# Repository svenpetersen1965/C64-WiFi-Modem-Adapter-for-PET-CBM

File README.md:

# C64-WiFi-Modem-Adapter for the Commodore PET/CBM computers
This is an adapter for connecting a <a href="https://github.com/svenpetersen1965/C64-WiFi-Modem-User-Port">C64 WiFi-Modem</a> to the PET/CBM User Port.

The power obtained from the Cassette Port via the <a href="https://github.com/svenpetersen1965/C64-Diagnostic-Rev.-586220-Harness/tree/master/Diag586220_Harness/Diag586220_Cassette_Port">Cassette Port Dongle</a> from the diagnostic harness for the C64.

The terminal program that was used for testing is <a href="https://github.com/ChartreuseK/PETTERM/releases">PETTERM0.5.0</a>

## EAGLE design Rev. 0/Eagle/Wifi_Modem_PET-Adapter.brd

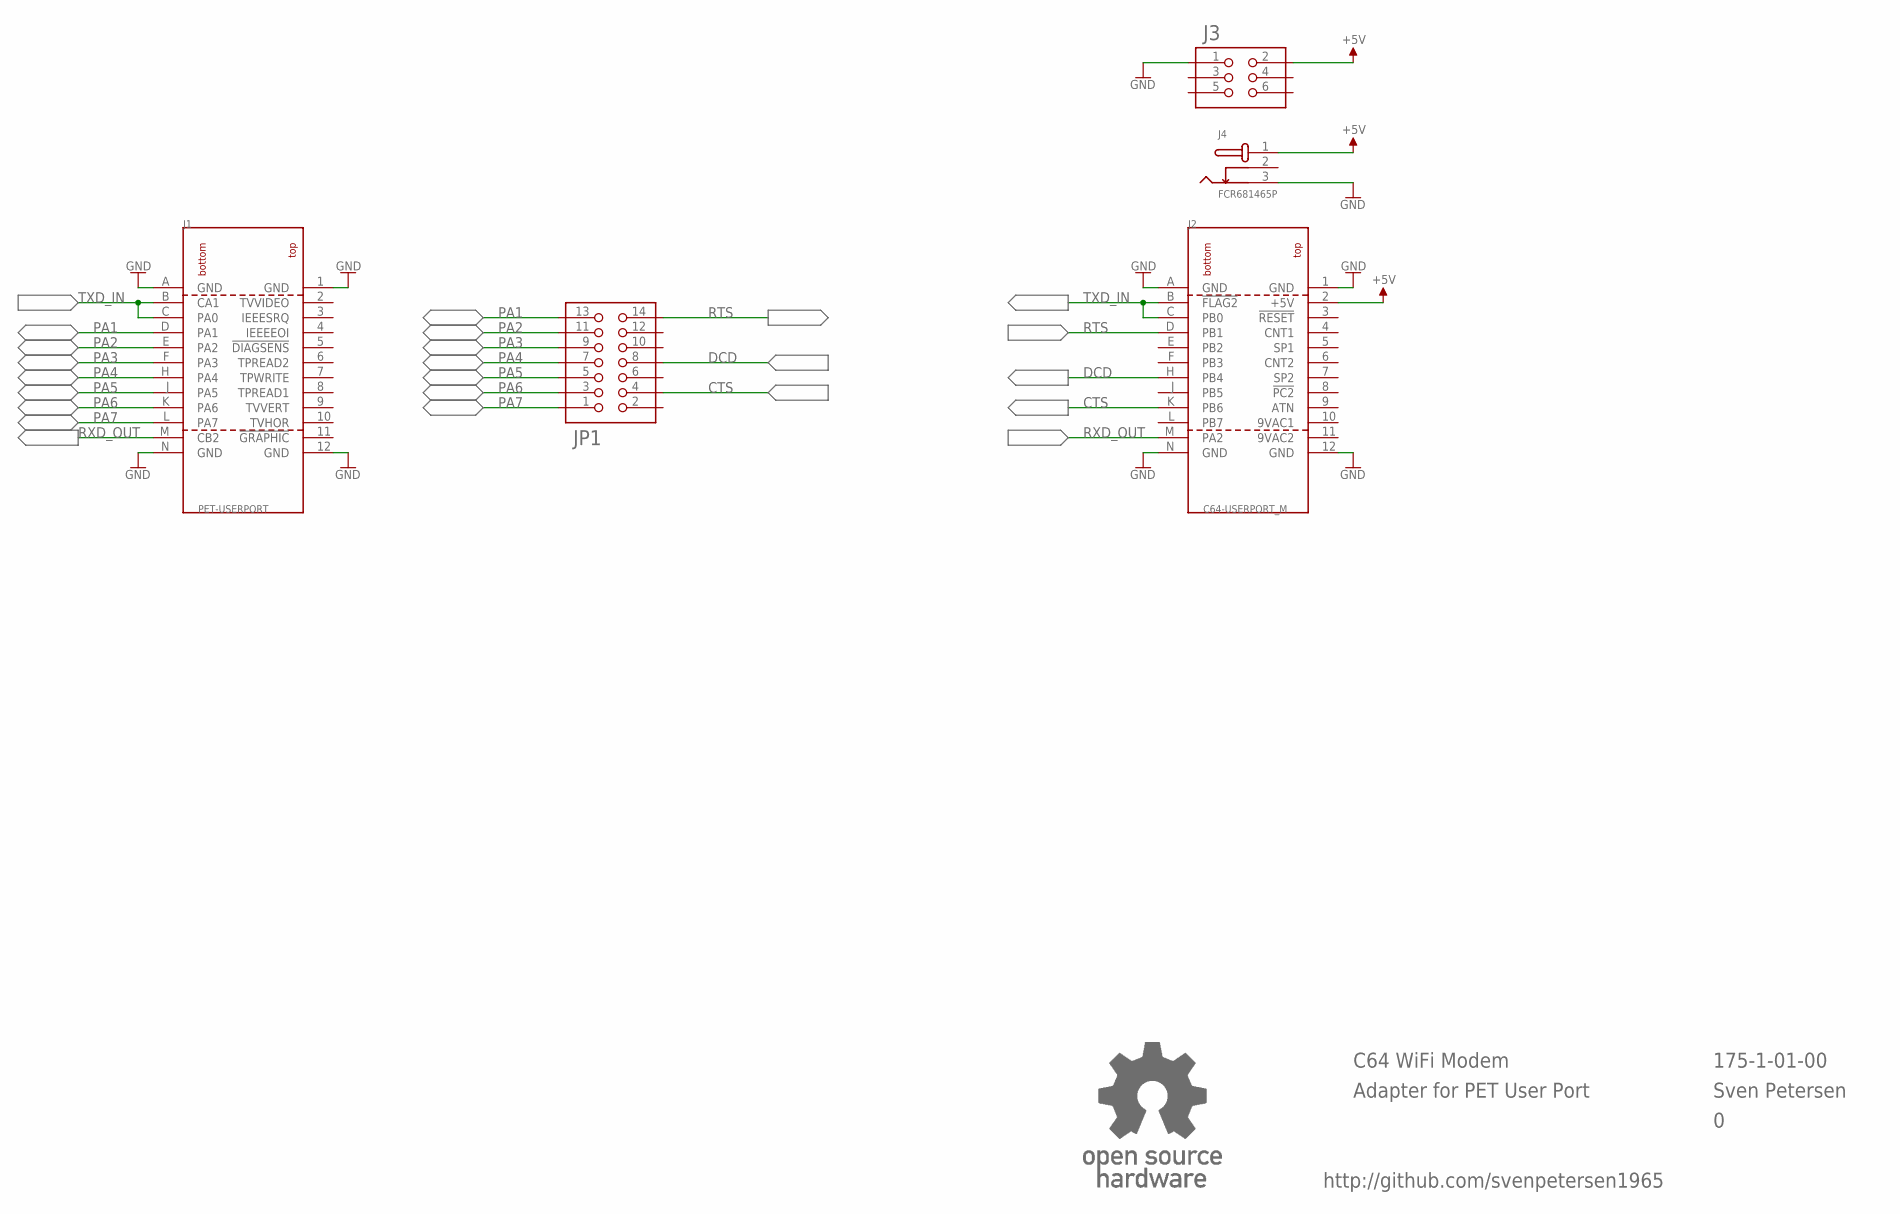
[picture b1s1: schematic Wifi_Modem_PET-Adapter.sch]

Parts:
J1: PET-USERPORT; USERPORT
J2: C64-USERPORT_M; USERPORT_M
J3: 2X03WV
J4: FCR681465P
JP1: PINHD-2X7; 2X07
U$2: OPEN_SOURCE_HW; OPENHW

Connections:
9VAC1: J2.10 (9VAC1)
9VAC2: J2.11 (9VAC2)
+5V: J2.2 (+5V), J3.2, J4.1
CTS: J2.K (PB6), JP1.4
DCD: J2.H (PB4), JP1.8
GND: J1.1 (GND), J1.12 (GND), J1.A (GND), J1.N (GND), J2.1 (GND), J2.12 (GND), J2.A (GND), J2.N (GND), J3.1, J4.3
PA1: J1.D (PA1), JP1.13
PA2: J1.E (PA2), JP1.11
PA3: J1.F (PA3), JP1.9
PA4: J1.H (PA4), JP1.7
PA5: J1.J (PA5), JP1.5
PA6: J1.K (PA6), JP1.3
PA7: J1.L (PA7), JP1.1
RTS: J2.D (PB1), JP1.14
RXD_OUT: J1.M (CB2), J2.M (PA2)
TXD_IN: J1.B (CA1), J1.C (PA0), J2.B (!FLAG2), J2.C (PB0)

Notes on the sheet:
C64 WiFi Modem
Adapter for PET User Port
Sven Petersen
175-1-01-00
http://github.com/svenpetersen1965

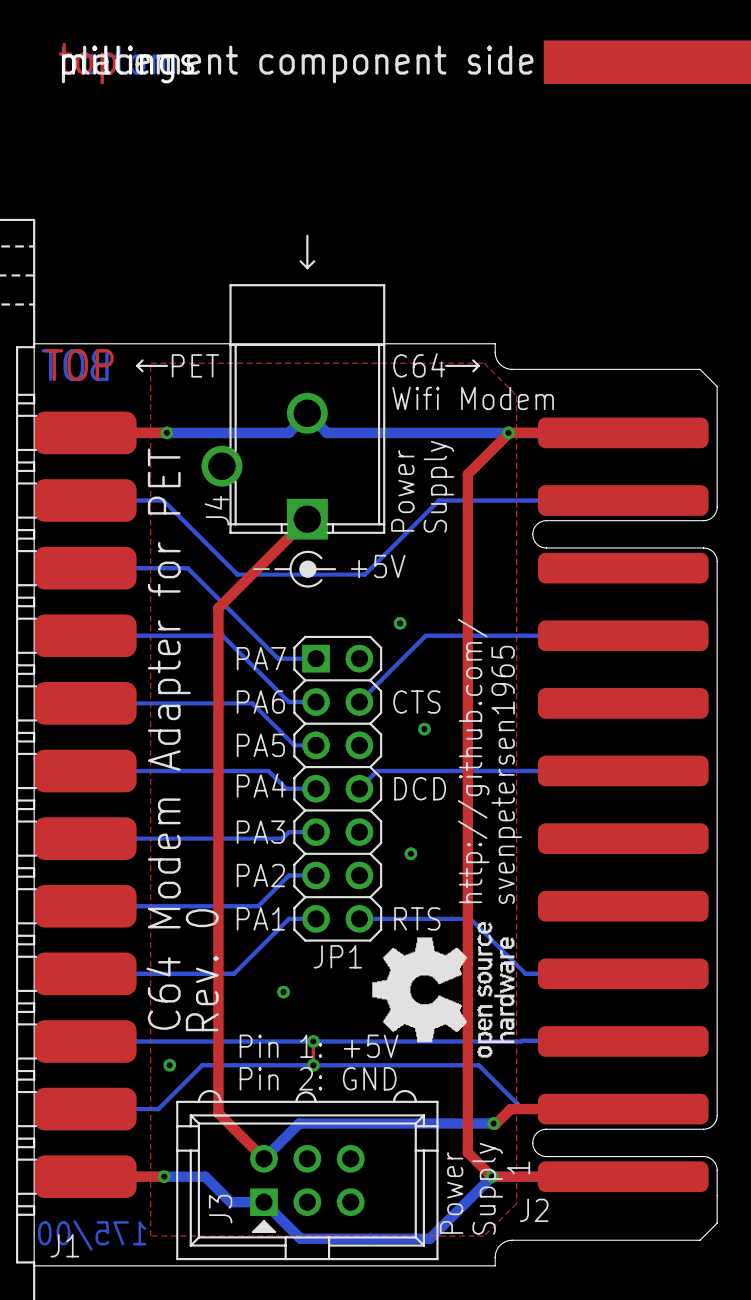
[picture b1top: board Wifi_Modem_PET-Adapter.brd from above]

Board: 2 copper layers, 40.0 x 72.1 mm, 8 parts (0 on the bottom side), 14 nets.

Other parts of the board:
U$40: 2LAYER
U$41: PCB-TITLE/

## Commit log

2021-05-12 Initial release
2021-05-28 Adding the cassette dongle label
    The label for the cassette dongle with a Commodore logo was added to the SVG. This way, there is a label, which is more neutral than the C64 and VIC-20 diagnostic labels for the cassette dongle and f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
2021-06-03 Labels added as PNG
